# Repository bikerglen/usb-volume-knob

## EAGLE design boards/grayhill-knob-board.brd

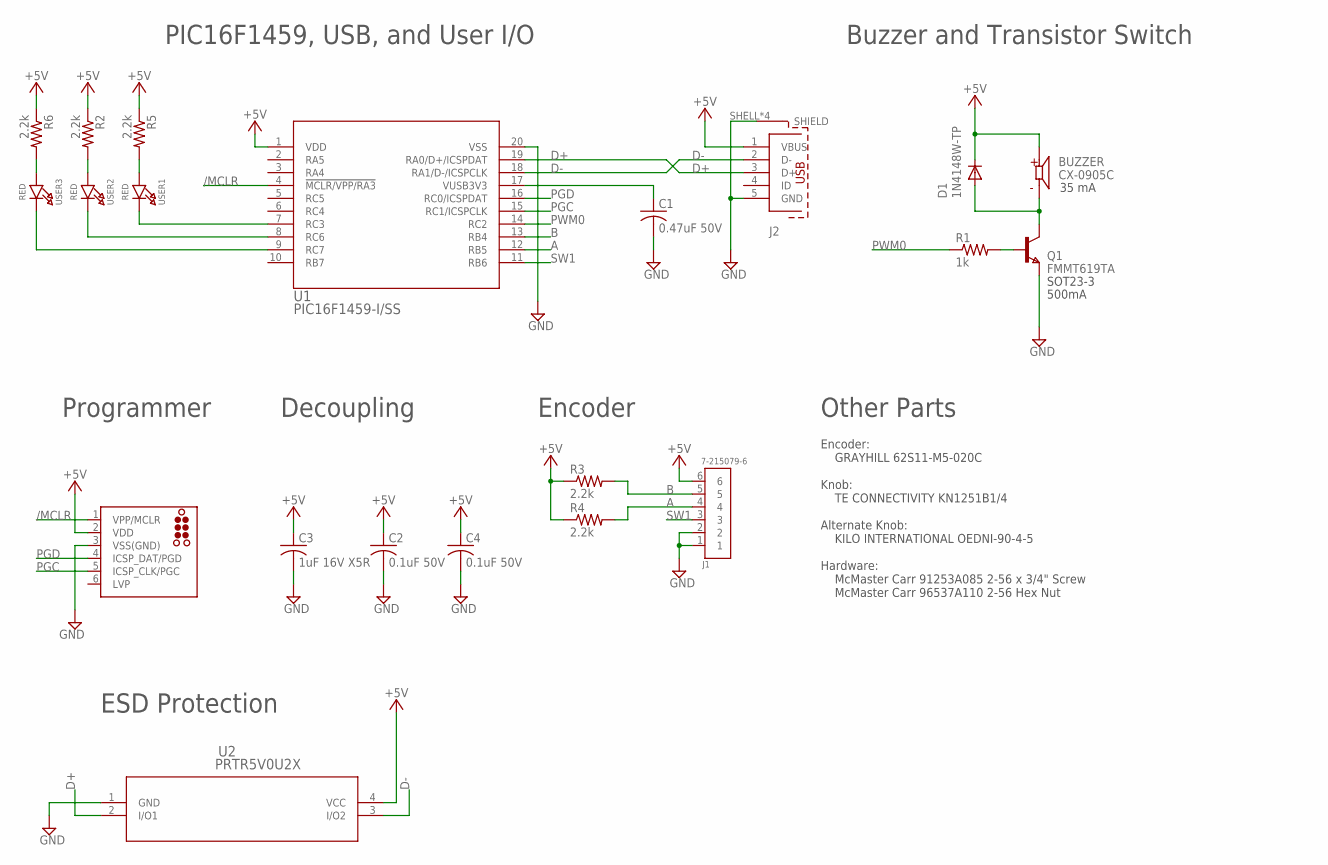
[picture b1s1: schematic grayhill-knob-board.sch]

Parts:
BUZZER: CX-0905C; CUI_CX-0905C
C1: 0.47uF 50V; C1206K; MFR_PART_NO C1206C474K5RACTU
C2, C4: 0.1uF 50V; C1206K; MFR_PART_NO C1206S104M5RACTU
C3: 1uF 16V X5R; C1210; MFR_PART_NO C1210C105K4PACTU
D1: 1N4148W-TP; SOD123
J1: 7-215079-6; TE_7-215079-6
J2: 629105136821
J3: TC2030-MCP-NL
Q1: FMMT619TA; SOT-23
R1: 1k; R0805
R2, R3, R4, R5, R6: 2.2k; R0805
U1: PIC16F1459-I/SS; SSOP20_MC
U2: PRTR5V0U2X; SOT143B
USER1, USER2, USER3: RED; CHIPLED_0805_NOOUTLINE

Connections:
+5V: BUZZER.P, C2.1, C3.1, C4.1, D1.C, J1.6, J2.1 (VBUS), J3.2 (VDD), R2.1, R3.1, R4.1, R5.1, R6.1, U1.1 (VDD), U2.4 (VCC)
/MCLR: J3.1 (VPP/MCLR), U1.4 (!MCLR/VPP/RA3)
A: J1.4, R4.2, U1.12 (RB5)
B: J1.5, R3.2, U1.13 (RB4)
D+: J2.3 (D+), U1.19 (RA0/D+/ICSPDAT), U2.2 (I/O1)
D-: J2.2 (D-), U1.18 (RA1/D-/ICSPCLK), U2.3 (I/O2)
GND: C1.2, C2.2, C3.2, C4.2, J1.1, J1.2, J2.5 (GND), J2.SHELL (SHIELD), J2.SHELL1 (SHIELD), J2.SHELL2 (SHIELD), J2.SHELL3 (SHIELD), J3.3 (VSS(GND)), Q1.2 (E), U1.20 (VSS), U2.1 (GND)
unnamed: R6.2, USER3.A
unnamed: R2.2, USER2.A
unnamed: R5.2, USER1.A
unnamed: Q1.3 (B), R1.2
OUT0: BUZZER.N, D1.A, Q1.1 (C)
PGC: J3.5 (ICSP_CLK/PGC), U1.15 (RC1/ICSPCLK)
PGD: J3.4 (ICSP_DAT/PGD), U1.16 (RC0/ICSPDAT)
PWM0: R1.1, U1.14 (RC2)
SW1: J1.3, U1.11 (RB6)
USER1: U1.7 (RC3), USER1.C
USER2: U1.8 (RC6), USER2.C
USER3: U1.9 (RC7), USER3.C
VUSB: C1.1, U1.17 (VUSB3V3)

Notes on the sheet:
SOT23-3
500mA
PIC16F1459, USB, and User I/O
Buzzer and Transistor Switch
Programmer
Decoupling
35 mA
ESD Protection
Encoder
Encoder: GRAYHILL 62S11-M5-020C Knob: TE CONNECTIVITY KN1251B1/4 Alternate Knob: KILO INTERNATIONAL OEDNI-90-4-5 Hardware: McMaster Carr 91253A085 2-56 x 3/4" Screw McMaster Carr 96537A110 2-56 Hex Nut
Other Parts

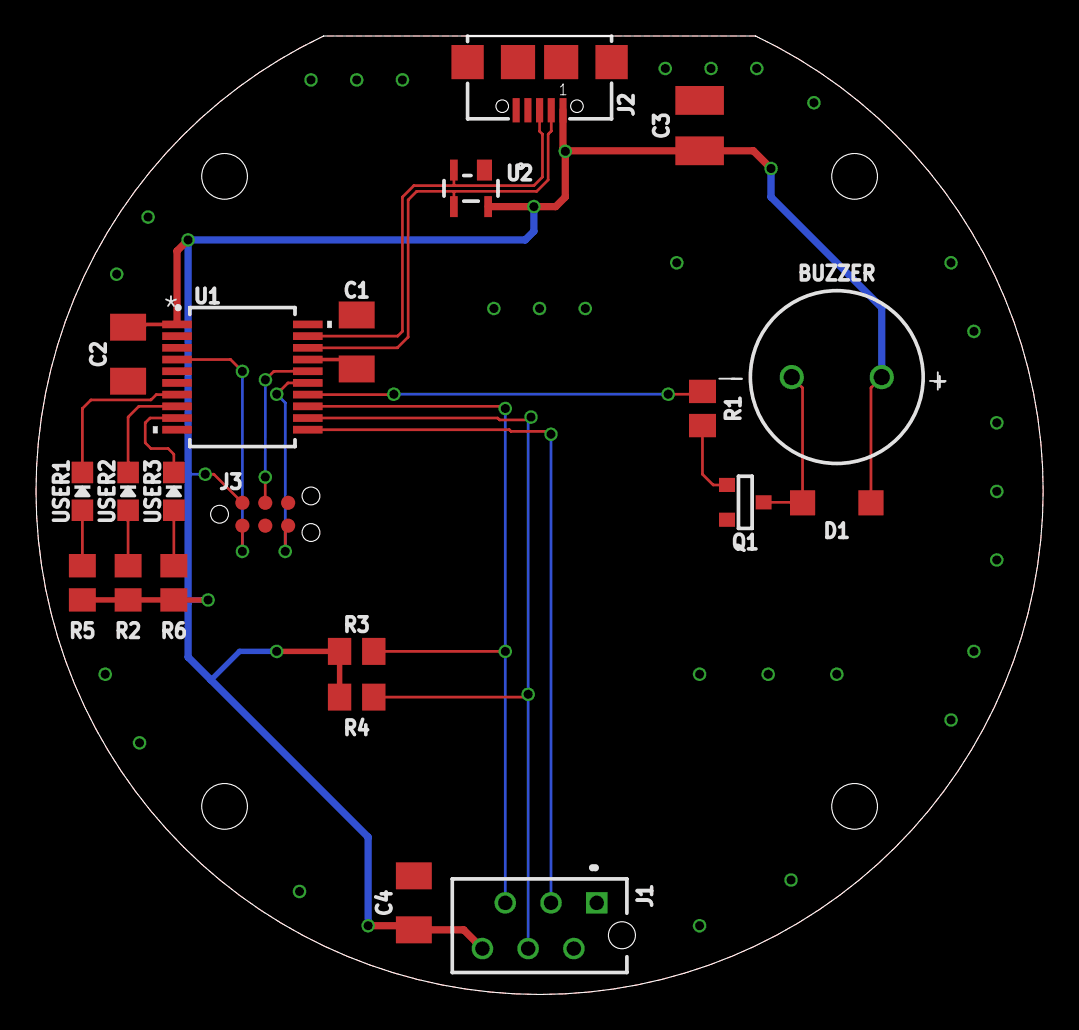
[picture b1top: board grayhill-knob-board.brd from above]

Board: 2 copper layers, 56.0 x 53.2 mm, 21 parts (0 on the bottom side), 20 nets.

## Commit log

2020-03-15 initial checkin

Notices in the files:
parts and their libraries:
InputOutputIO: Copyright: Würth Elektronik
tag-connect: ©2009 ROFA.cz - modified and updated by Robert Darlington ‹rdarlington@gmail.com›
microbuilder: This work is placed in the public domain, and may be freely used for commercial and non-commercial work with the following conditions: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
